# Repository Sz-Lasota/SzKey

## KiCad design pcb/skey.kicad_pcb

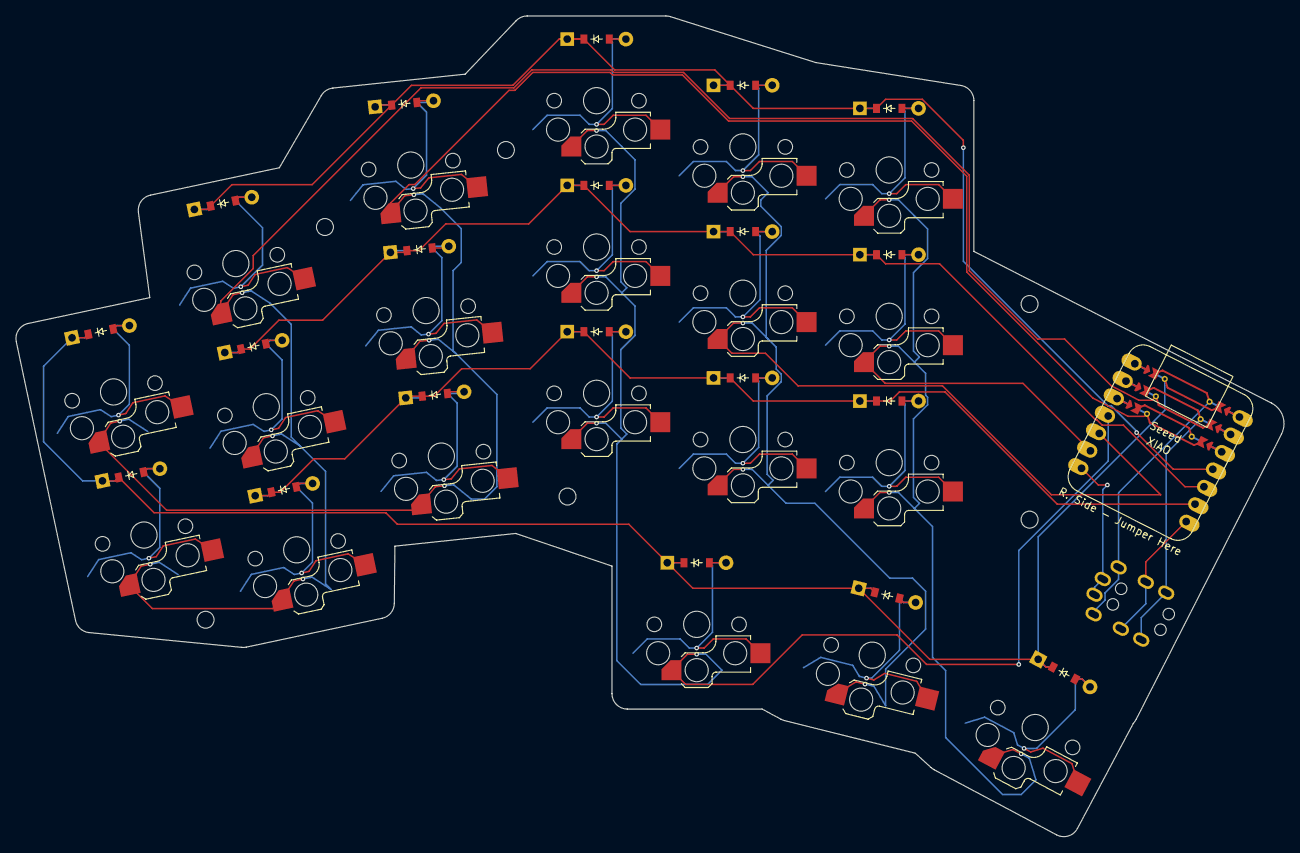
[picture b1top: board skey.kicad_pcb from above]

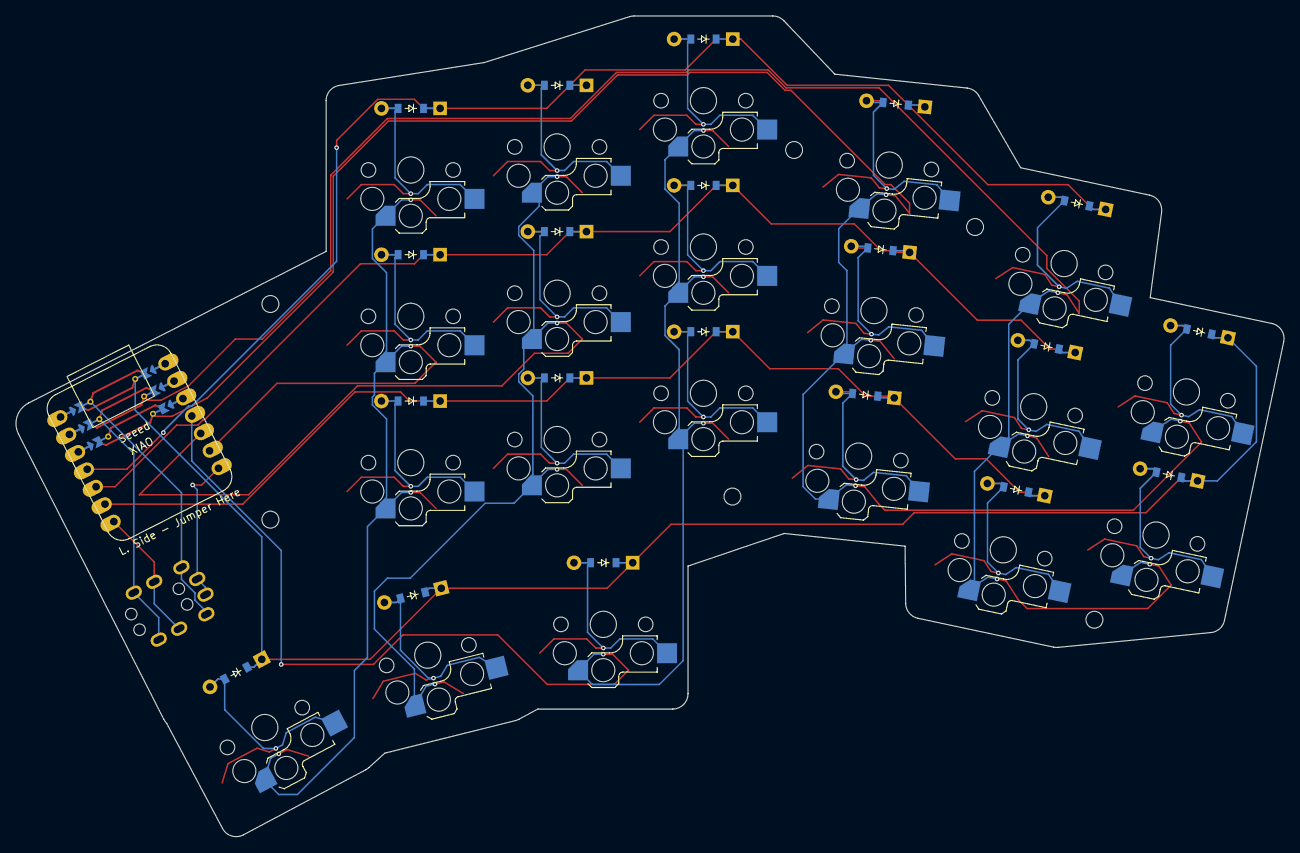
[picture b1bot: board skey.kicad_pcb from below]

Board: 2 copper layers, 164.7 x 106.6 mm, 47 parts (20 on the bottom side), 29 nets.

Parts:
D1, D2, D3, D4, D5, D6, D7, D8, D9, D10, D11, D12, D13, D14, D15, D16, D17, D18, D19, D20: ComboDiode
MH1, MH2, MH3, MH4, MH5, MH6: mounting_hole_npth
S1, S2, S3, S4, S5, S6, S7, S8, S9, S10, S11, S12, S13, S14, S15, S16, S17, S18, S19, S20: switch_choc_v1_v2
TRRS1: trrs_pj320a (reversible)

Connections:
P0: D1.1, D2.1, D18.1, D19.1, D20.1
P1: S1.1, S3.1, S4.1, S5.1
P2: S2.1, S6.1, S7.1, S8.1
P3: S9.1, S10.1, S11.1, S18.1
P4: S12.1, S13.1, S14.1, S19.1
P5: S15.1, S16.1, S17.1, S20.1
P8: D3.1, D6.1, D9.1, D12.1, D15.1
P9: D4.1, D7.1, D10.1, D13.1, D16.1
P10: D5.1, D8.1, D11.1, D14.1, D17.1
far_thumb: D20.2, S20.2
home_thumb: D19.2, S19.2
index_bottom: D12.2, S12.2
index_middle: D13.2, S13.2
index_top: D14.2, S14.2
inner_bottom: D15.2, S15.2
inner_middle: D16.2, S16.2
inner_top: D17.2, S17.2
middle_bottom: D9.2, S9.2
middle_middle: D10.2, S10.2
middle_top: D11.2, S11.2
near_thumb: D18.2, S18.2
outer_bottom: D1.2, S1.2
outer_middle: D2.2, S2.2
pinky_bottom: D3.2, S3.2
pinky_middle: D4.2, S4.2
pinky_top: D5.2, S5.2
ring_bottom: D6.2, S6.2
ring_middle: D7.2, S7.2
ring_top: D8.2, S8.2

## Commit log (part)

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2026-04-13 Updated keyboard pcb
2026-04-15 xiao footprint
2026-04-15 Choc switches
2026-04-16 Mounting holes
2026-04-20 Skey pcb
